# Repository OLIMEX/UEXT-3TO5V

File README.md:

# UEXT-3TO5V
UEXT to UEXT converter from 3V host to 5V devices

https://www.olimex.com/Products/Modules/Adapters/UEXT-3TO5V/open-source-hardware

## Licensee
* Hardware is released under CERN Open Hardware Licence Version 2 - Strongly Reciprocal
* Documentation is released under CC BY-SA 4.0

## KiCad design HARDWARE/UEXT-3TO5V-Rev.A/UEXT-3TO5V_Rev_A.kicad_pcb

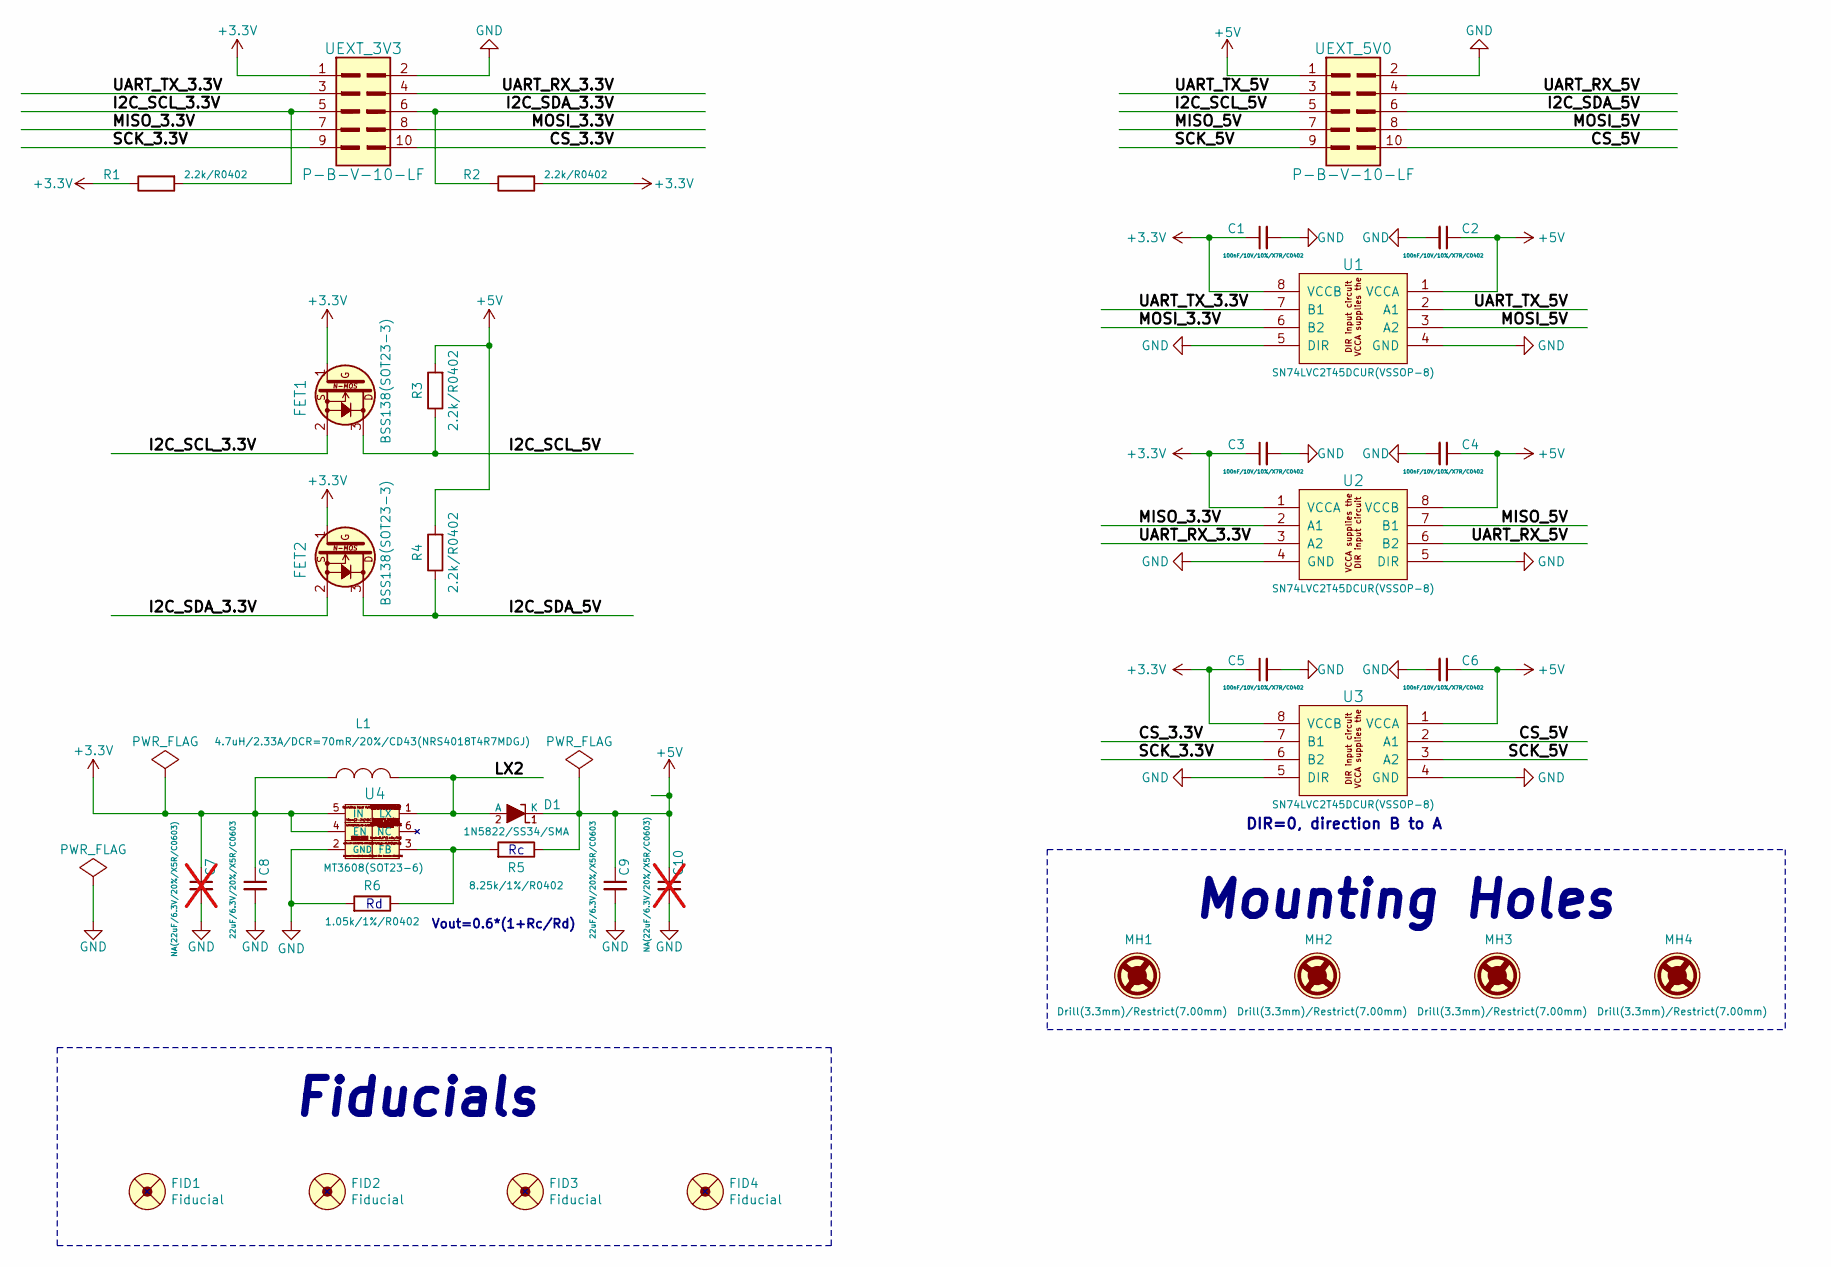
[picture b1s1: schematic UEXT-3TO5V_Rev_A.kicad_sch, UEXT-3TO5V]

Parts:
C1, C2, C3, C4, C5, C6: 100nF/10V/10%/X7R/C0402; C_0402_5MIL_DWS
C7, C10: NA(22uF/6.3V/20%/X5R/C0603); C_0603_5MIL_DWS; not fitted
C8, C9: 22uF/6.3V/20%/X5R/C0603; C_0603_5MIL_DWS
D1: 1N5822/SS34/SMA; SMA-KA
FET1, FET2: BSS138(SOT23-3); SOT23
FID1, FID3: Fiducial; Fiducial1x3
FID2, FID4: Fiducial; Fiducial1x3_Paste
L1: 4.7uH/2.33A/DCR=70mR/20%/CD43(NRS4018T4R7MDGJ); CD42(43)
MH1, MH2, MH3, MH4: Drill(3.3mm)/Restrict(7.00mm); Mounting_Hole_Drill-3.3mm_Clerance-7mm
R1, R2, R3, R4: 2.2k/R0402; R_0402_5MIL_DWS
R5: 8.25k/1%/R0402; R_0402_5MIL_DWS
R6: 1.05k/1%/R0402; R_0402_5MIL_DWS
U1, U2, U3: SN74LVC2T45DCUR(VSSOP-8); VSSOP-8_Pitch-0.50mm_Pad-0.25mm_Dimensions-2.30x2.00x1.00mm
U4: MT3608(SOT23-6); SOT23-6
UEXT_3V3, UEXT_5V0: P-B-V-10-LF; GBH-254-SMT-10

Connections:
+3.3V: C1.1, C3.1, C5.1, C7.1, C8.1, FET1.1 (G), FET2.1 (G), L1.2, R1.1, R2.2, U1.8 (VCCB), U2.1 (VCCA), U3.8 (VCCB), U4.4 (EN), U4.5 (IN), UEXT_3V3.1
+5V: C2.1, C4.1, C6.1, C9.1, C10.1, D1.1 (K), R3.2, R4.2, R5.1, U1.1 (VCCA), U2.8 (VCCB), U3.1 (VCCA), UEXT_5V0.1
/CS_3.3V: U3.7 (B1), UEXT_3V3.10
/CS_5V: U3.2 (A1), UEXT_5V0.10
/I2C_SCL_3.3V: FET1.2 (S), R1.2, UEXT_3V3.5
/I2C_SCL_5V: FET1.3 (D), R3.1, UEXT_5V0.5
/I2C_SDA_3.3V: FET2.2 (S), R2.1, UEXT_3V3.6
/I2C_SDA_5V: FET2.3 (D), R4.1, UEXT_5V0.6
/LX2: D1.2 (A), L1.1, U4.1 (LX)
/MISO_3.3V: U2.2 (A1), UEXT_3V3.7
/MISO_5V: U2.7 (B1), UEXT_5V0.7
/MOSI_3.3V: U1.6 (B2), UEXT_3V3.8
/MOSI_5V: U1.3 (A2), UEXT_5V0.8
/SCK_3.3V: U3.6 (B2), UEXT_3V3.9
/SCK_5V: U3.3 (A2), UEXT_5V0.9
/UART_RX_3.3V: U2.3 (A2), UEXT_3V3.4
/UART_RX_5V: U2.6 (B2), UEXT_5V0.4
/UART_TX_3.3V: U1.7 (B1), UEXT_3V3.3
/UART_TX_5V: U1.2 (A1), UEXT_5V0.3
GND: C1.2, C2.2, C3.2, C4.2, C5.2, C6.2, C7.2, C8.2, C9.2, C10.2, R6.2, U1.4 (GND), U1.5 (DIR), U2.4 (GND), U2.5 (DIR), U3.4 (GND), U3.5 (DIR), U4.2 (GND), UEXT_3V3.2, UEXT_5V0.2
unnamed: R5.2, R6.1, U4.3 (FB)

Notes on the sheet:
DIR=0, direction B to A
Mounting Holes
Fiducials
Vout=0.6*(1+Rc/Rd)

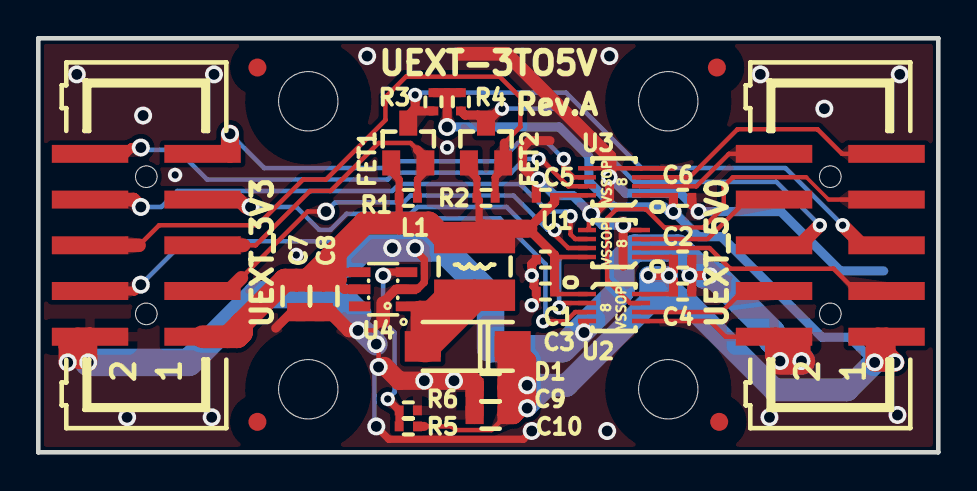
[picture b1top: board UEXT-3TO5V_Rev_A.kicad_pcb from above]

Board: 2 copper layers, 50.0 x 23.0 mm, 41 parts (7 on the bottom side), 21 nets.

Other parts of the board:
Logo_OLIMEX_TB-Top: Logo_OLIMEX_TB
Sign_Antistatic: Sign_Antistatic
Sign_CE: CE_Sign
Sign_OSHW_8x8: Sign_OSHW_8x8
Sign_PB-Free: Sign_PB-Free
Sign_RecycleBin: Sign_RecycleBin; Sign_RecycleBin_1
Sign_RoHS: Sign_RoHS; Sign_RoHS_1

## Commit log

2025-06-04 initial upload

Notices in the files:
HARDWARE/UEXT-3TO5V-Rev.A/UEXT-3TO5V_Rev_A.kicad_pcb:
(C) 2025
